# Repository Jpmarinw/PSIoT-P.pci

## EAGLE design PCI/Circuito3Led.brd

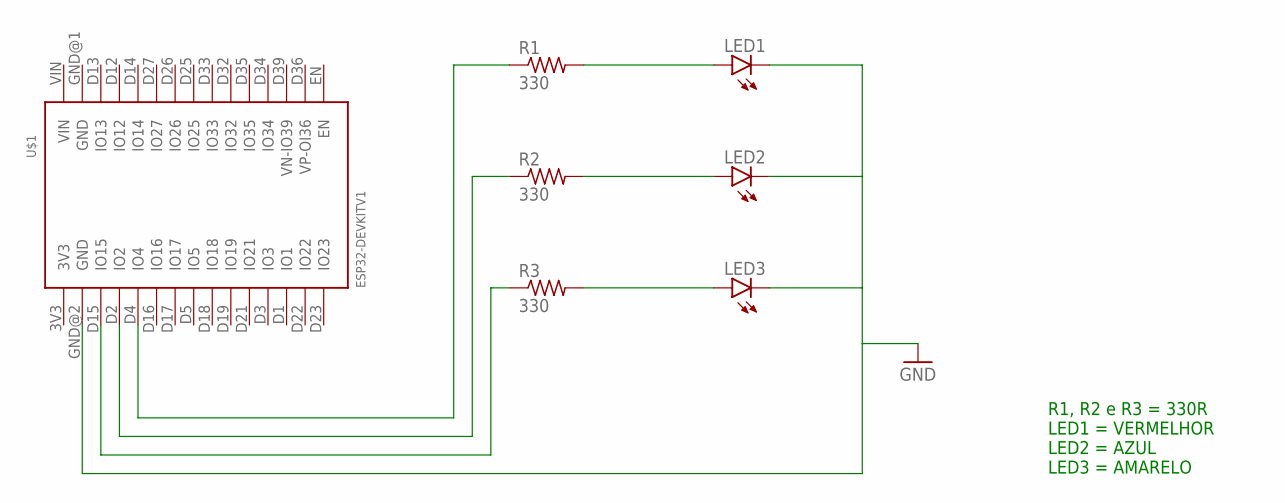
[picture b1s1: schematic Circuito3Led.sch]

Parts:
LED1, LED2, LED3: LED5MM
R1, R2, R3: 330; 0204/7
U$1: ESP32DEVKITV1; ESP32-DEVKITV1

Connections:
GND: LED1.K (C), LED2.K (C), LED3.K (C), U$1.GND@2 (GND)
unnamed: R3.1, U$1.D15 (IO15)
unnamed: R2.1, U$1.D2 (IO2)
unnamed: R1.1, U$1.D4 (IO4)
unnamed: LED1.A, R1.2
unnamed: LED2.A, R2.2
unnamed: LED3.A, R3.2

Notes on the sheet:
R1, R2 e R3 = 330R LED1 = VERMELHOR LED2 = AZUL LED3 = AMARELO

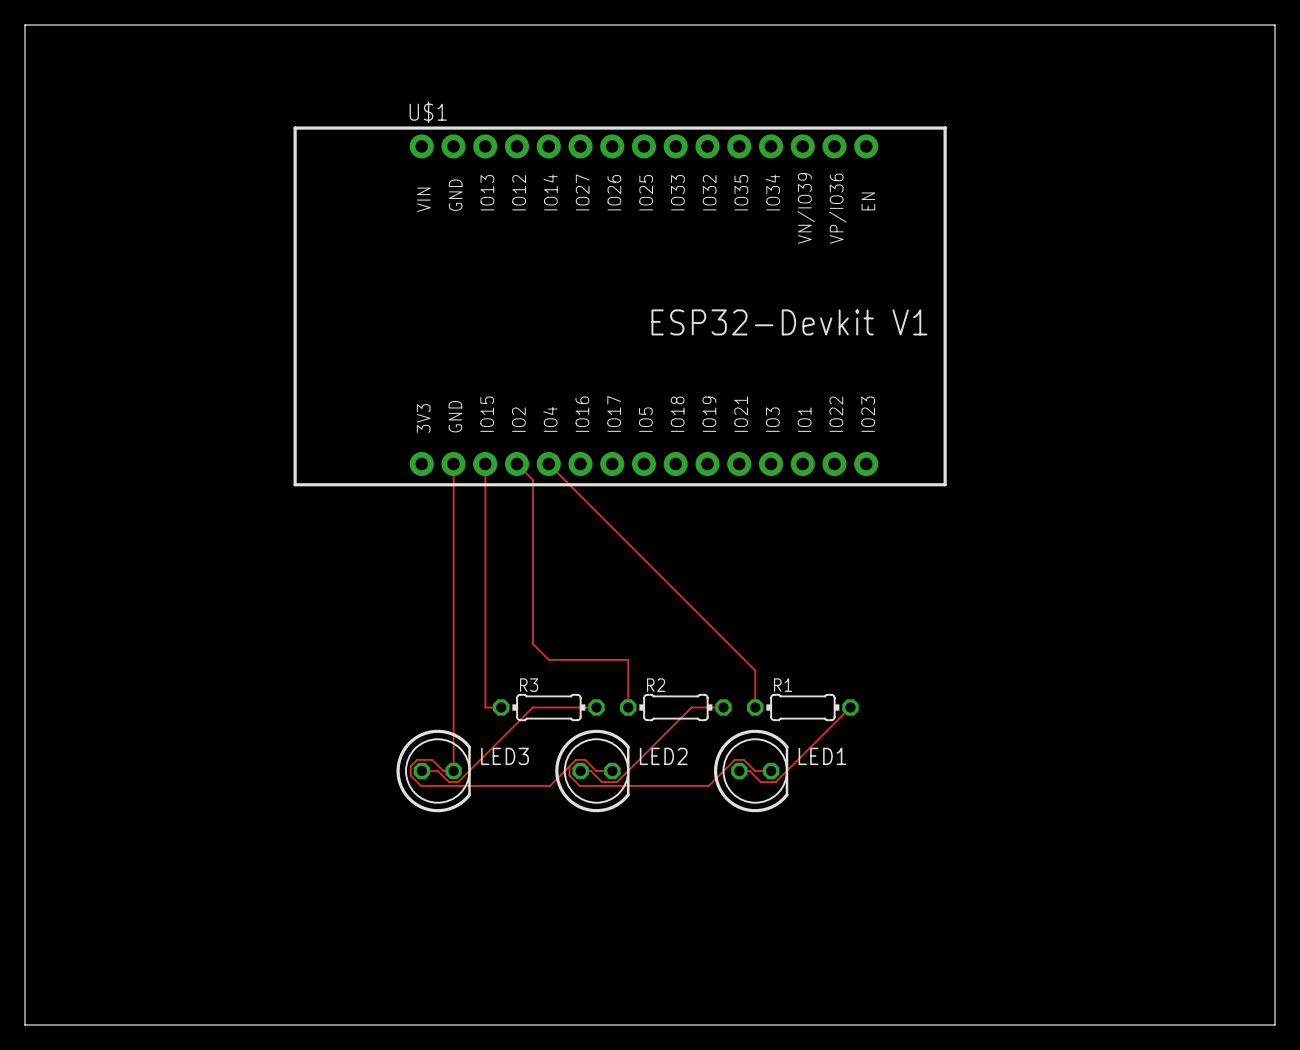
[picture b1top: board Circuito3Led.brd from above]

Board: 2 copper layers, 100.0 x 80.0 mm, 7 parts (0 on the bottom side), 7 nets.

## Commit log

2024-03-28 Primeiro commit
2024-03-30 Segundo commit
